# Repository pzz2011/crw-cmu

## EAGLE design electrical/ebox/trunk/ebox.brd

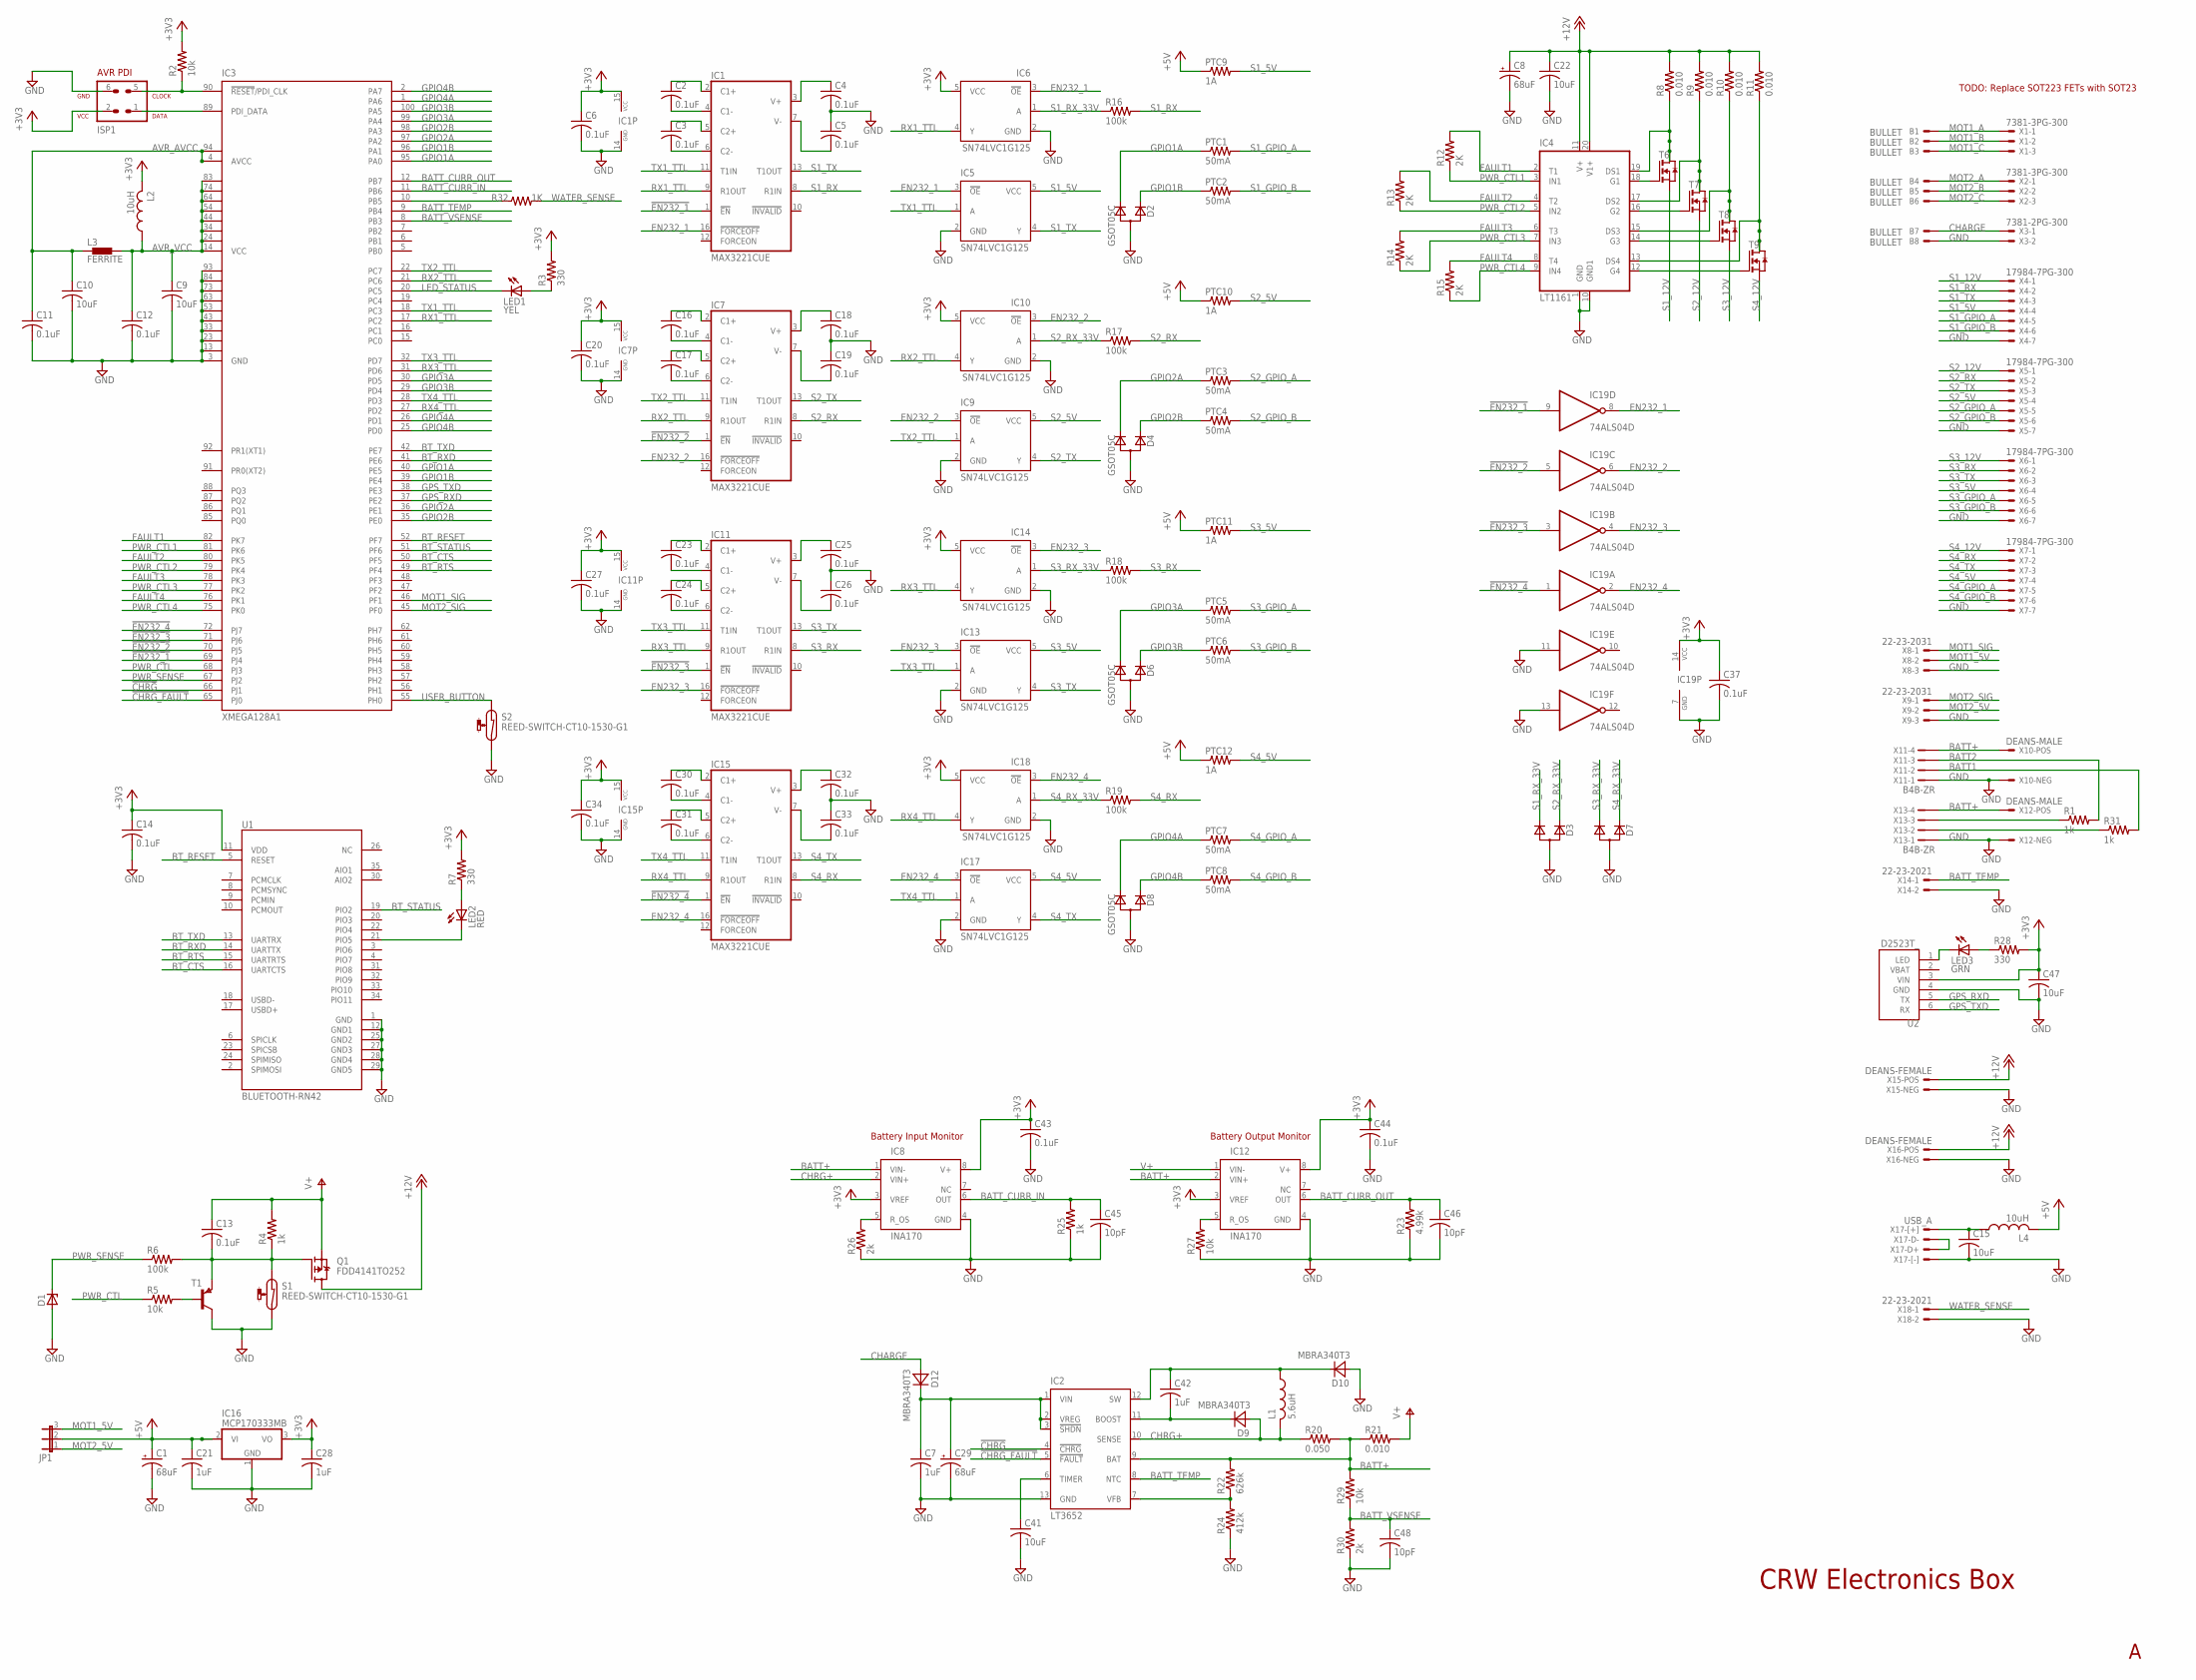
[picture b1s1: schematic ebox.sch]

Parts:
B1, B2, B3, B4, B5, B6, B7, B8: BULLET
C1, C8, C29: 68uF; PANASONIC_D
C2, C3, C4, C5, C6, C11, C12, C13, C14, C16, C17, C18, C19, C20, C23, C24, C25, C26, C27, C30, C31, C32, C33, C34, C37, C43, C44: 0.1uF; C0805
C7, C21, C28, C42: 1uF; C0805
C9, C10, C15, C22, C41, C47: 10uF; C0805
C45, C46, C48: 10pF; C0805
D1: ZENER-DIODESOT23; SOT23
D2, D4, D6, D8: GSOT05C; SOT-23
D3, D7: D_2CSOT23; SOT-23
D9, D10, D12: MBRA340T3; SMA
IC1, IC7, IC11, IC15: MAX3221CUE; TSSOP16
IC2: LT3652; MSOP12-MSE
IC3: XMEGA128A1; TQFP100
IC4: LT1161; SOIC20R
IC5, IC6, IC9, IC10, IC13, IC14, IC17, IC18: SN74LVC1G125; SOT23-DBV
IC8, IC12: INA170; MSOP8
IC16: MCP170333MB; SOT89
IC19: 74ALS04D; SO14
ISP1: AVR-PDIVERT; AVR-ISP-6
JP1: JP2E; JP2
L1: 5.6uH; IHLP-2020CZ-11
L2, L4: 10uH; L2012C
L3: FERRITE; 0402
LED1: YEL; CHIPLED_1206
LED2: RED; CHIPLED_1206
LED3: GRN; CHIPLED_1206
PTC1, PTC2, PTC3, PTC4, PTC5, PTC6, PTC7, PTC8: 50mA; R1206
PTC9, PTC10, PTC11, PTC12: 1A; R1206
Q1: FDD4141TO252; TO252
R1, R4, R25, R31: 1k; R0805
R2, R5, R27, R29: 10k; R0805
R3, R7, R28: 330; R0805
R6, R16, R17, R18, R19: 100k; R0805
R8, R9, R10, R11, R21: 0.010; R6332
R12, R13, R14, R15: 2K; R0805
R20: 0.050; R6332
R22: 626k; R0805
R23: 4.99k; R0805
R24: 412k; R0805
R26, R30: 2k; R0805
R32: 1K; R0805
S1, S2: REED-SWITCH-CT10-1530-G1; CT10-G1
T1: PNPSOT23; SOT-23
T6, T7, T8, T9: NMOSSOT23-6; SOT23-6
U1: BLUETOOTH-RN42; RN41
U2: D2523T_; EM406
X1, X2: 7381-3PG-300
X3: 7381-2PG-300
X4, X5, X6, X7: 17984-7PG-300
X8, X9: 22-23-2031
X10, X12: DEANS-MALE; DEANS_MALE
X11, X13: B4B-ZR
X14: 22-23-2021
X15, X16: DEANS-FEMALE; DEANS_FEMALE
X17: USB_A; 1001-002-01100
X18: 22-23-2021; MPN 22-23-2021

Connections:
3ROU: IC4.18 (G1), T6.4 (G)
!CHRG: IC2.4 (!CHRG), IC3.66 (PJ1)
!CHRG_FAULT: IC2.5 (!FAULT), IC3.65 (PJ0)
!EN232_1: IC1.1 (!EN), IC3.69 (PJ4), IC19.9 (I)
!EN232_2: IC3.70 (PJ5), IC7.1 (!EN), IC19.5 (I)
!EN232_3: IC3.71 (PJ6), IC11.1 (!EN), IC19.3 (I)
!EN232_4: IC3.72 (PJ7), IC15.1 (!EN), IC19.1 (I)
+3V3: C6.1, C14.1, C20.1, C27.1, C28.1, C34.1, C37.1, C43.1, C44.1, C47.1, IC1.15 (VCC), IC6.5 (VCC), IC7.15 (VCC), IC8.3 (VREF), IC8.8 (V+), IC10.5 (VCC), IC11.15 (VCC), IC12.3 (VREF), IC12.8 (V+), IC14.5 (VCC), IC15.15 (VCC), IC16.3 (VO), IC18.5 (VCC), IC19.14 (VCC), ISP1.2, L2.2, R2.2, R3.2, R7.2, R28.2, U1.11 (VDD), U2.3 (VIN)
+5V: C1.+, C21.1, IC16.2 (VI), IC16.2@1 (VI1), JP1.2, L4.2, PTC9.1, PTC10.1, PTC11.1, PTC12.1
+12V: C8.+, C22.1, IC4.11 (V+), IC4.20 (V1+), Q1.3 (D), R8.2, R9.2, R10.2, R11.2, X15.POS, X16.POS
AVR_AVCC: C10.1, C11.1, IC3.4 (AVCC), IC3.94 (AVCC1), L3.1
AVR_VCC: C9.1, C12.1, IC3.14 (VCC), IC3.24 (VCC1), IC3.34 (VCC2), IC3.44 (VCC3), IC3.54 (VCC4), IC3.64 (VCC5), IC3.74 (VCC6), IC3.83 (VCC7), L2.1, L3.2
BATT1: R31.2, X11.2
BATT2: R1.2, X11.3
BATT+: IC2.9 (BAT), IC8.1 (VIN-), IC12.2 (VIN+), R20.2, R21.1, R22.2, R29.2, X10.POS, X11.4, X12.POS, X13.4
BATT_CURR_IN: C45.1, IC3.11 (PB6), IC8.6 (OUT), R25.2
BATT_CURR_OUT: C46.1, IC3.12 (PB7), IC12.6 (OUT), R23.2
BATT_TEMP: IC2.8 (NTC), IC3.9 (PB4), X14.1
BATT_VSENSE: C48.1, IC3.8 (PB3), R29.1, R30.2
BT_CTS: IC3.50 (PF5), U1.16 (UARTCTS)
BT_RESET: IC3.52 (PF7), U1.5 (RESET)
BT_RTS: IC3.49 (PF4), U1.15 (UARTRTS)
BT_RXD: IC3.41 (PE6), U1.14 (UARTTX)
BT_STATUS: IC3.51 (PF6), U1.19 (PIO2)
BT_TXD: IC3.42 (PE7), U1.13 (UARTRX)
CHARGE: B7.P$1, D12.A, X3.1
CHRG+: D9.A, IC2.10 (SENSE), IC8.2 (VIN+), L1.2, R20.1
EN232_1: IC1.16 (!FORCEOFF), IC5.3 (!OE), IC6.3 (!OE), IC19.8 (O)
EN232_2: IC7.16 (!FORCEOFF), IC9.3 (!OE), IC10.3 (!OE), IC19.6 (O)
EN232_3: IC11.16 (!FORCEOFF), IC13.3 (!OE), IC14.3 (!OE), IC19.4 (O)
EN232_4: IC15.16 (!FORCEOFF), IC17.3 (!OE), IC18.3 (!OE), IC19.2 (O)
FAULT1: IC3.82 (PK7), IC4.2 (T1), R12.2
FAULT2: IC3.80 (PK5), IC4.4 (T2), R13.2
FAULT3: IC3.78 (PK3), IC4.6 (T3), R14.2
FAULT4: IC3.76 (PK1), IC4.8 (T4), R15.2
GND: B8.P$1, C1.-, C4.2, C5.1, C6.2, C7.2, C8.-, C9.2, C10.2, C11.2, C12.2, C14.2, C15.2, C18.2, C19.1, C20.2, C21.2, C22.2, C25.2, C26.1, C27.2, C28.2, C29.-, C32.2, C33.1, C34.2, C37.2, C41.2, C43.2, C44.2, C45.2, C46.2, C47.2, C48.2, D1.1 (A), D2.1 (A), D3.1 (A), D4.1 (A), D6.1 (A), D7.1 (A), D8.1 (A), D10.A, IC1.14 (GND), IC2.13 (GND), IC3.3 (GND), IC3.13 (GND1), IC3.23 (GND2), IC3.33 (GND3), IC3.43 (GND4), IC3.53 (GND5), IC3.63 (GND6), IC3.73 (GND7), IC3.84 (GND8), IC3.93 (GND9), IC4.1 (GND), IC4.10 (GND1), IC5.2 (GND), IC6.2 (GND), IC7.14 (GND), IC8.4 (GND), IC9.2 (GND), IC10.2 (GND), IC11.14 (GND), IC12.4 (GND), IC13.2 (GND), IC14.2 (GND), IC15.14 (GND), IC16.1 (GND), IC17.2 (GND), IC18.2 (GND), IC19.7 (GND), IC19.11 (I), IC19.13 (I), ISP1.6, R23.1, R24.1, R25.1, R26.1, R27.1, R30.1, S1.2, S2.2, T1.1 (C), U1.1 (GND), U1.12 (GND1), U1.25 (GND2), U1.27 (GND3), U1.28 (GND4), U1.29 (GND5), U2.4 (GND), X3.2, X4.7, X5.7, X6.7, X7.7, X8.3, X9.3, X10.NEG, X11.1, X12.NEG, X13.1, X14.2, X15.NEG, X16.NEG, X17.4, X18.2
GPIO1A: D2.3 (C2), IC3.40 (PE5), IC3.95 (PA0), PTC1.1
GPIO1B: D2.2 (C1), IC3.39 (PE4), IC3.96 (PA1), PTC2.1
GPIO2A: D4.3 (C2), IC3.36 (PE1), IC3.97 (PA2), PTC3.1
GPIO2B: D4.2 (C1), IC3.35 (PE0), IC3.98 (PA3), PTC4.1
GPIO3A: D6.3 (C2), IC3.30 (PD5), IC3.99 (PA4), PTC5.1
GPIO3B: D6.2 (C1), IC3.29 (PD4), IC3.100 (PA5), PTC6.1
GPIO4A: D8.3 (C2), IC3.1 (PA6), IC3.26 (PD1), PTC7.1
GPIO4B: D8.2 (C1), IC3.2 (PA7), IC3.25 (PD0), PTC8.1
GPS_RXD: IC3.37 (PE2), U2.5 (TX)
GPS_TXD: IC3.38 (PE3), U2.6 (RX)
LED_STATUS: IC3.20 (PC5), LED1.C
LED_STATUS1: LED2.C, U1.21 (PIO5)
MOT1_5V: JP1.3, X8.2
MOT1_A: B1.P$1, X1.1
MOT1_B: B2.P$1, X1.2
MOT1_C: B3.P$1, X1.3
MOT1_SIG: IC3.46 (PF1), X8.1
MOT2_5V: JP1.1, X9.2
MOT2_A: B4.P$1, X2.1
MOT2_B: B5.P$1, X2.2
MOT2_C: B6.P$1, X2.3
MOT2_SIG: IC3.45 (PF0), X9.1
unnamed: C2.2, IC1.4 (C1-)
unnamed: C2.1, IC1.2 (C1+)
unnamed: C3.1, IC1.5 (C2+)
unnamed: C3.2, IC1.6 (C2-)
unnamed: IC3.90 (!RESET!/PDI_CLK), ISP1.5, R2.1
unnamed: LED1.A, R3.1
unnamed: IC3.89 (PDI_DATA), ISP1.1
unnamed: R5.2, T1.3 (B)
unnamed: LED2.A, R7.1
unnamed: C4.1, IC1.3 (V+)
unnamed: C5.2, IC1.7 (V-)
unnamed: IC4.19 (DS1), R8.1, T6.1 (D), T6.2 (D1), T6.5 (D2), T6.6 (D3)
unnamed: C13.2, Q1.1 (G), R4.1, R6.2, S1.1, T1.2 (E)
unnamed: IC4.17 (DS2), R9.1, T7.1 (D), T7.2 (D1), T7.5 (D2), T7.6 (D3)
unnamed: IC4.15 (DS3), R10.1, T8.1 (D), T8.2 (D1), T8.5 (D2), T8.6 (D3)
unnamed: IC4.13 (DS4), R11.1, T9.1 (D), T9.2 (D1), T9.5 (D2), T9.6 (D3)
unnamed: IC3.10 (PB5), R32.1
unnamed: IC4.16 (G2), T7.4 (G)
unnamed: IC4.14 (G3), T8.4 (G)
unnamed: IC4.12 (G4), T9.4 (G)
unnamed: C16.2, IC7.4 (C1-)
unnamed: C16.1, IC7.2 (C1+)
unnamed: C17.2, IC7.6 (C2-)
unnamed: C17.1, IC7.5 (C2+)
unnamed: C18.1, IC7.3 (V+)
unnamed: C19.2, IC7.7 (V-)
unnamed: C23.2, IC11.4 (C1-)
unnamed: C23.1, IC11.2 (C1+)
unnamed: C24.2, IC11.6 (C2-)
unnamed: C24.1, IC11.5 (C2+)
unnamed: C25.1, IC11.3 (V+)
unnamed: C26.2, IC11.7 (V-)
unnamed: C30.2, IC15.4 (C1-)
unnamed: C30.1, IC15.2 (C1+)
unnamed: C31.2, IC15.6 (C2-)
unnamed: C31.1, IC15.5 (C2+)
unnamed: C32.1, IC15.3 (V+)
unnamed: C33.2, IC15.7 (V-)
unnamed: C41.1, IC2.6 (TIMER)
unnamed: C15.1, L4.1, X17.1
unnamed: C42.2, D9.C, IC2.11 (BOOST)
unnamed: C42.1, D10.C, IC2.12 (SW), L1.1
unnamed: LED3.C, U2.1 (LED)
unnamed: IC2.7 (VFB), R22.1, R24.2
unnamed: X17.2, X17.3
unnamed: R1.1, X13.3
unnamed: C7.1, C29.+, D12.C, IC2.1 (VIN), IC2.2 (VREG), IC2.3 (!SHDN)
unnamed: IC8.5 (R_OS), R26.2
unnamed: IC12.5 (R_OS), R27.2
unnamed: LED3.A, R28.1
unnamed: R31.1, X13.2
PWR_CTL: IC3.68 (PJ3), R5.1
PWR_CTL1: IC3.81 (PK6), IC4.3 (IN1), R12.1
PWR_CTL2: IC3.79 (PK4), IC4.5 (IN2), R13.1
PWR_CTL3: IC3.77 (PK2), IC4.7 (IN3), R14.1
PWR_CTL4: IC3.75 (PK0), IC4.9 (IN4), R15.1
PWR_SENSE: D1.3 (C), IC3.67 (PJ2), R6.1
RX1_TTL: IC1.9 (R1OUT), IC3.17 (PC2), IC6.4 (Y)
RX2_TTL: IC3.21 (PC6), IC7.9 (R1OUT), IC10.4 (Y)
RX3_TTL: IC3.31 (PD6), IC11.9 (R1OUT), IC14.4 (Y)
RX4_TTL: IC3.27 (PD2), IC15.9 (R1OUT), IC18.4 (Y)
S1_5V: IC5.5 (VCC), PTC9.2, X4.4
S1_12V: T6.3 (S), X4.1
S1_GPIO_A: PTC1.2, X4.5
S1_GPIO_B: PTC2.2, X4.6
S1_RX: IC1.8 (R1IN), R16.2, X4.2
S1_RX_33V: D3.3 (C2), IC6.1 (A), R16.1
S1_TX: IC1.13 (T1OUT), IC5.4 (Y), X4.3
S2_5V: IC9.5 (VCC), PTC10.2, X5.4
S2_12V: T7.3 (S), X5.1
S2_GPIO_A: PTC3.2, X5.5
S2_GPIO_B: PTC4.2, X5.6
S2_RX: IC7.8 (R1IN), R17.2, X5.2
S2_RX_33V: D3.2 (C1), IC10.1 (A), R17.1
S2_TX: IC7.13 (T1OUT), IC9.4 (Y), X5.3
S3_5V: IC13.5 (VCC), PTC11.2, X6.4
S3_12V: T8.3 (S), X6.1
S3_GPIO_A: PTC5.2, X6.5
S3_GPIO_B: PTC6.2, X6.6
S3_RX: IC11.8 (R1IN), R18.2, X6.2
S3_RX_33V: D7.3 (C2), IC14.1 (A), R18.1
S3_TX: IC11.13 (T1OUT), IC13.4 (Y), X6.3
S4_5V: IC17.5 (VCC), PTC12.2, X7.4
S4_12V: T9.3 (S), X7.1
S4_GPIO_A: PTC7.2, X7.5
S4_GPIO_B: PTC8.2, X7.6
S4_RX: IC15.8 (R1IN), R19.2, X7.2
S4_RX_33V: D7.2 (C1), IC18.1 (A), R19.1
S4_TX: IC15.13 (T1OUT), IC17.4 (Y), X7.3
TX1_TTL: IC1.11 (T1IN), IC3.18 (PC3), IC5.1 (A)
TX2_TTL: IC3.22 (PC7), IC7.11 (T1IN), IC9.1 (A)
TX3_TTL: IC3.32 (PD7), IC11.11 (T1IN), IC13.1 (A)
TX4_TTL: IC3.28 (PD3), IC15.11 (T1IN), IC17.1 (A)
USER_BUTTON: IC3.55 (PH0), S2.1
V+: C13.1, IC12.1 (VIN-), Q1.2 (S), R4.2, R21.2
WATER_SENSE: R32.2, X18.1

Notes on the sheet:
CRW Electronics Box
Battery Input Monitor
Battery Output Monitor
TODO: Replace SOT223 FETs with SOT23

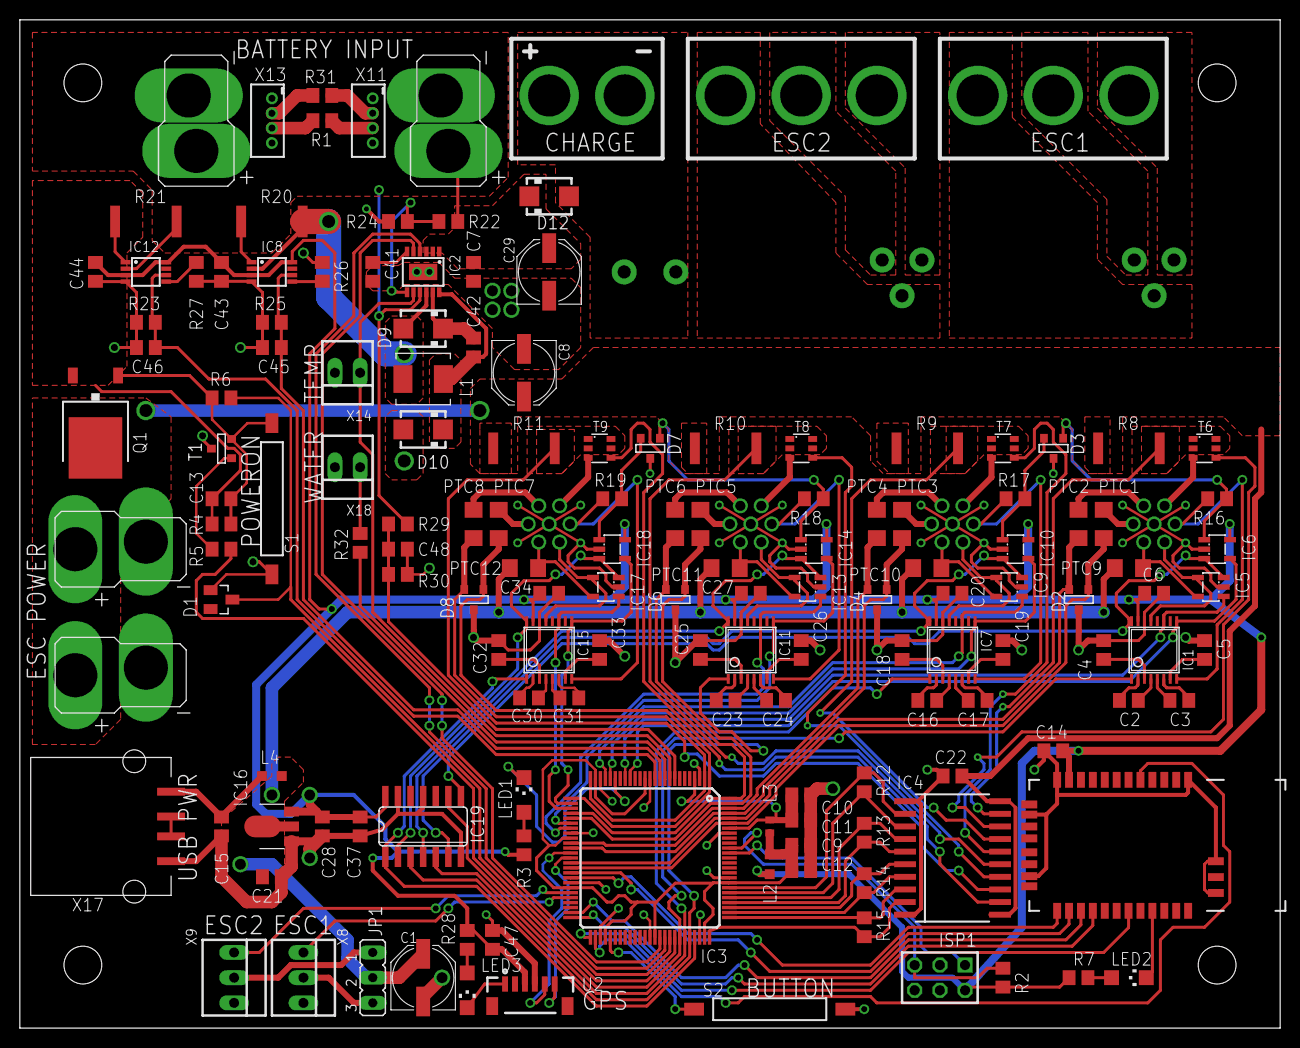
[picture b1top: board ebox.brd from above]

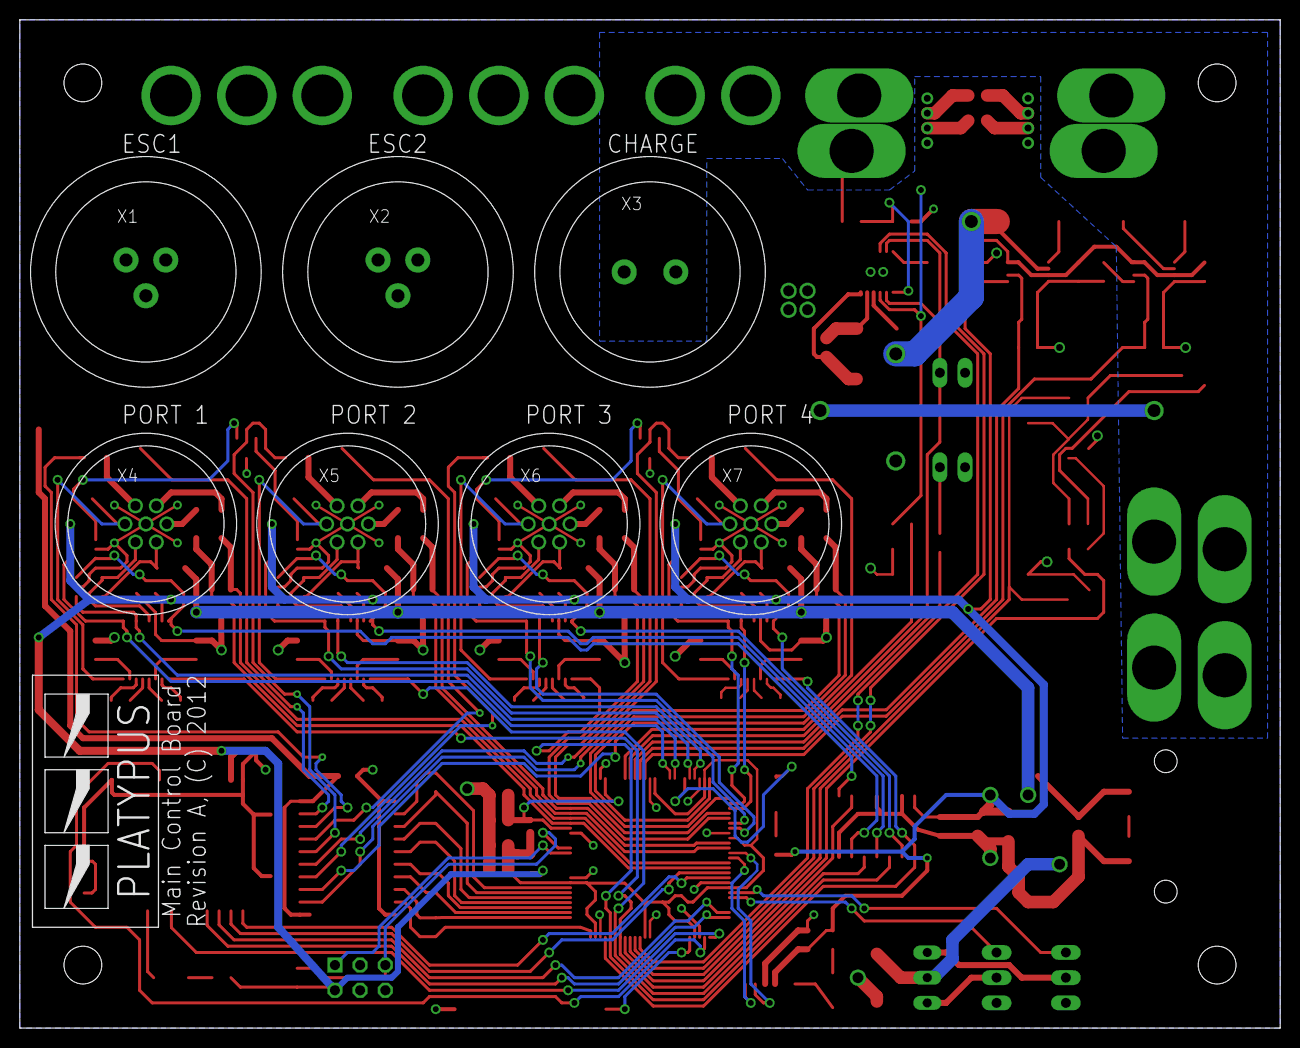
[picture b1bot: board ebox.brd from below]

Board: 2 copper layers, 127.0 x 101.6 mm, 162 parts (8 on the bottom side), 154 nets.

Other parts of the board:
U$1: PLATYPUS_LOGO; PLATYPUS_LOGO_SMALL

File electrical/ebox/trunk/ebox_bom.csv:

"Qty";"Value";"Device";"Package";"Parts";"Description";"MF";"MPN";"OC_FARNELL";"OC_NEWARK";
"2";"";"D_2CSOT23";"SOT-23";"D3, D7";"Dual DIODE";"";"";"unknown";"unknown";
"1";"";"JP2E";"JP2";"JP1";"JUMPER";"";"";"";"";
"4";"";"NMOSSOT23-6";"SOT23-6";"T6, T7, T8, T9";"MOS FET";"";"";"unknown";"unknown";
"1";"";"PNPSOT23";"SOT-23";"T1";"PNP TRANSISTOR";"";"DSS20200L-7";"unknown";"25R4554";
"1";"";"ZENER-DIODESOT23";"SOT23";"D1";"Z-Diode";"";"";"";"";
"5";"0.010";"R-US_R6332";"R6332";"R8, R9, R10, R11, R21";"RESISTOR, American symbol";"";"";"";"";
"1";"0.050";"R-US_R6332";"R6332";"R20";"RESISTOR, American symbol";"";"";"";"";
"27";"0.1uF";"C-USC0805";"C0805";"C2, C3, C4, C5, C6, C11, C12, C13, C14, C16, C17, C18, C19, C20, C23, C24, C25, C26, C27, C30, C31, C32, C33, C34, C37, C43, C44";"CAPACITOR, American symbol";"";"";"";"";
"5";"100k";"R-US_R0805";"R0805";"R6, R16, R17, R18, R19";"RESISTOR, American symbol";"";"";"";"";
"4";"10k";"R-US_R0805";"R0805";"R2, R5, R27, R29";"RESISTOR, American symbol";"";"";"";"";
"3";"10pF";"C-USC0805";"C0805";"C45, C46, C48";"CAPACITOR, American symbol";"";"";"";"";
"6";"10uF";"C-USC0805";"C0805";"C9, C10, C15, C22, C41, C47";"CAPACITOR, American symbol";"";"";"";"";
"2";"10uH";"L-USL2012C";"L2012C";"L2, L4";"INDUCTOR, American symbol";"";"";"";"";
"4";"17984-7PG-300";"17984-7PG-300";"17984-7PG-300";"X4, X5, X6, X7";"MICRO-CON-X® FIELD INSTALLABLE CONNECTOR";"";"";"";"";
"4";"1A";"R-US_R1206";"R1206";"PTC9, PTC10, PTC11, PTC12";"RESISTOR, American symbol";"";"";"";"";
"1";"1K";"R-US_R0805";"R0805";"R32";"RESISTOR, American symbol";"";"";"";"";
"4";"1k";"R-US_R0805";"R0805";"R1, R4, R25, R31";"RESISTOR, American symbol";"";"";"";"";
"4";"1uF";"C-USC0805";"C0805";"C7, C21, C28, C42";"CAPACITOR, American symbol";"";"";"";"";
"2";"22-23-2021";"22-23-2021";"22-23-2021";"X14, X18";".100" (2.54mm) Center Header - 2 Pin";"MOLEX";"22-23-2021";"1462926";"25C3832";
"2";"22-23-2031";"22-23-2031";"22-23-2031";"X8, X9";".100" (2.54mm) Center Header - 3 Pin";"MOLEX";"22-23-2031";"1462950";"30C0862";
"4";"2K";"R-US_R0805";"R0805";"R12, R13, R14, R15";"RESISTOR, American symbol";"";"";"";"";
"2";"2k";"R-US_R0805";"R0805";"R26, R30";"RESISTOR, American symbol";"";"";"";"";
"3";"330";"R-US_R0805";"R0805";"R3, R7, R28";"RESISTOR, American symbol";"";"";"";"";
"1";"4.99k";"R-US_R0805";"R0805";"R23";"RESISTOR, American symbol";"";"";"";"";
"1";"412k";"R-US_R0805";"R0805";"R24";"RESISTOR, American symbol";"";"";"";"";
"1";"5.6uH";"IHLP-2020CZ-11";"IHLP-2020CZ-11";"L1";"";"";"";"";"";
"8";"50mA";"R-US_R1206";"R1206";"PTC1, PTC2, PTC3, PTC4, PTC5, PTC6, PTC7, PTC8";"RESISTOR, American symbol";"";"";"";"";
"1";"626k";"R-US_R0805";"R0805";"R22";"RESISTOR, American symbol";"";"";"";"";
"3";"68uF";"CPOL-USD";"PANASONIC_D";"C1, C8, C29";"POLARIZED CAPACITOR, American symbol";"";"";"";"";
"1";"7381-2PG-300";"7381-2PG-300";"7381-2PG-300";"X3";"";"";"";"";"";
"2";"7381-3PG-300";"7381-3PG-300";"7381-3PG-300";"X1, X2";"Mini-Con-X Panel Connector";"";"";"";"";
"1";"74ALS04D";"74ALS04D";"SO14";"IC19";"Hex INVERTER";"";"";"";"";
"1";"AVR-PDIVERT";"AVR-PDIVERT";"AVR-ISP-6";"ISP1";"AVR PDI programming interface connector";"";"";"";"";
"2";"B4B-ZR";"B4B-ZR";"B4B-ZR";"X11, X13";"ZH CONNECTOR 1.5 mm, 4 pin 1 row";"FARNELL";"B4B-ZR(LF)(SN)";"1830916";"37K9960";
"1";"BLUETOOTH-RN42";"BLUETOOTH-RN41"";"RN41";"U1";"Bluetooth SMD module";"";"";"";"";
"8";"BULLET";"BULLET";"BULLET";"B1, B2, B3, B4, B5, B6, B7, B8";"Bullet Connector";"";"";"";"";
"1";"D2523T_";"D2523T_";"EM406";"U2";"D2523T GPS Module";"";"";"";"";
"2";"DEANS-FEMALE";"DEANS-FEMALE";"DEANS_FEMALE";"X15, X16";"Deans Battery Connector";"";"";"";"";
"2";"DEANS-MALE";"DEANS-MALE";"DEANS_MALE";"X10, X12";"Deans Battery Connector";"";"";"";"";
"1";"FDD4141TO252";"FDD4141TO252";"TO252";"Q1";"P-Channel PowerTrench® MOSFET";"";"";"";"";
"1";"FERRITE";"BML15HB121SN1";"0402";"L3";"EMIFIL (R) Chip Ferrite Bead for GHz Noise";"";"";"";"";
"1";"GRN";"LEDCHIPLED_1206";"CHIPLED_1206";"LED3";"LED";"";"";"";"";
"4";"GSOT05C";"D_2CSOT23";"SOT-23";"D2, D4, D6, D8";"Dual DIODE";"";"";"unknown";"unknown";
"2";"INA170";"INA170";"MSOP8";"IC8, IC12";"High-Side, Bidirectional";"";"";"";"";
"1";"LT1161";"LT1161";"SOIC20R";"IC4";"Single-Supply 16-Bit Stereo ADC";"";"";"";"";
"1";"LT3652";"LT3652";"MSOP12-MSE";"IC2";"2-Channel, 12-Bit ADC with I2C-Compatible Interface 10-Lead MSOP";"";"AD7992BRMZ-0";"1078311";"31M4422";
"4";"MAX3221CUE";"MAX3221CUE";"TSSOP16";"IC1, IC7, IC11, IC15";"RS-232 Transceivers with AutoShutdown";"MAXIM";"MAX3221CUE+";"1379915";"68K4608";
"3";"MBRA340T3";"MBRA340T3";"SMA";"D9, D10, D12";"Surface Mount Schottky Power Rectifier";"";"";"";"";
"1";"MCP170333MB";"MCP170333MB";"SOT89";"IC16";"250 mA, 16V, Low Quiescent Current LDO Regulator";"";"";"";"";
"1";"PLATYPUS_LOGO";"PLATYPUS_LOGO";"PLATYPUS_LOGO_SMALL";"U$1";"";"";"";"";"";
"1";"RED";"LEDCHIPLED_1206";"CHIPLED_1206";"LED2";"LED";"";"";"";"";
"2";"REED-SWITCH-CT10-1530-G1";"REED-SWITCH-CT10-1530-G1";"CT10-G1";"S1, S2";"Reed Sensor";"COTO TECHNOLOGY";"CT10-1530-G1";"1081696";"";
"8";"SN74LVC1G125";"SN74LVC1G125";"SOT23-DBV";"IC5, IC6, IC9, IC10, IC13, IC14, IC17, IC18";"SINGLE BUS BUFFER GATE WITH 3-STATE OUTPUT";"";"";"";"";
"1";"USB_A";"USB_A";"1001-002-01100";"X17";"USB A-type connector";"";"";"";"";
"1";"XMEGA128A1";"XMEGA128A1";"TQFP100";"IC3";"MICROCONTROLLER";"";"";"unknown";"unknown";
"1";"YEL";"LEDCHIPLED_1206";"CHIPLED_1206";"LED1";"LED";"";"";"";"";

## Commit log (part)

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2012-11-01 Added board and some of layout.
2012-11-02 Added svn:ignore for temp files.
2012-11-02 I thought we just committed the changes to the footprints, but apparently we didn't.
2012-11-02 Adding tags and trunk structure to ebox.
2012-11-02 Moved ebox parts to trunk folder.
2012-11-02 We don't use avr7 microcontrollers.
2012-11-02 Made a tag of the point where system is feature complete, will be simplifying from here out.
2012-11-02 Removed switching regulators, replaced with onboard ESC BEC power.
2012-11-02 Added missing battery connectors for ESC.
2012-11-04 Added USB connector, swapped FETs for smaller form factor.
2012-11-07 Most of power layout is done too.
2012-11-13 Placed all components on board.
2012-11-16 Added rest of routing for much of power section.
2012-11-16 Loads better routing of power.
2012-11-16 Fixed sensor routing, couple of other things.
2012-11-16 More routing finished, under 100 airwires.
2012-11-18 All high power routing is sufficient. Tuning routing on digital lines.
2012-11-18 Almost all digital routing completed and checked. Need to do pwr ctrl and enable lines.
2012-11-18 All signal wiring to MCU stable. Just need to do enable lines and clean up.
2012-11-19 Added water sensor connection.
2012-11-19 Fixed last few airwires, on to trace optimization for a bit.
2012-11-19 Cleaned up more stuff. Just need to do final check and silkscreen work.
2012-11-19 Updated some silkscreen on various areas.
2012-11-19 Silkscreening complete. Prepped for DFM check.
2012-11-19 Fixed thermal reliefs in board.
2012-11-19 Gerber/excellon files for board.
2012-11-19 Oops, wrong component file.
2012-11-19 Fixed copper pour insufficient spacing issues.
2012-11-19 Updated for more DFM corrections.
2012-11-20 Added bill of materials.
2012-11-20 Added excel file with full parts list.
2012-11-20 Added as-built for revision A of ebox board.
2012-12-12 Added tag for last Arduino-based firmware, new firmware will be for custom PCBs.
2012-12-12 Added new source directory for firmware to handle all the new stuff. Changed build system to AVR.
2012-12-12 Moved all the source files to source directory.
2012-12-12 Moved cpp files to new source directory for firmware.
2012-12-12 Added main function as entry point.
2012-12-12 Renamed a whole bunch of source files to match new firmware organization.
2012-12-12 Added placeholder for board definition files.
2012-12-12 Adapted the Makefile to begin to do what we want.
2012-12-17 Changed old main file so syntax highlighting works.
2012-12-17 Removed windows-style line endings from serial header.
2012-12-17 Organized files into hardware and system folders to cleanup main source tree.
2012-12-17 Added header files for all the system components (previously automagically handled by Arduino?)
2012-12-17 Made modifications to add Netbeans project for the firmware. It is NOT required to compile the firmware.
2012-12-17 Cleaned up project configuration.
2012-12-21 Cleaned up project configuration more, added working LED driver, restructured netbeans project to actually show useful stuff.
2012-12-21 Added port of eeprom reads and writes, i think.
2012-12-21 Added better eeprom port.
2012-12-21 Ok, starting to get reasonably compilable. Still need to figure out how the heck to templatize serial stuff.
2012-12-25 Major overhaul to serial code structure that will hopefully resolve most of this mess with the multiple serial ports being used.
2012-12-25 Major overhaul to IO system. Trying to get things under control again w.r.t. firmware structure.
2012-12-25 Minor patch to get I2c driver in line.
2012-12-30 Added new cleaned up servo handling code, similar to serial fix. Just need to do the same for a timer callback and we should be in business.
2012-12-30 Added general purpose task timer (for regular execution of control loops). I think at this point we mostly just need to pipe it all up and cross our fingers.
2012-12-30 Added CPU frequency macro.
2012-12-30 Fixed board macro.
2012-12-30 Configured system to use 32Mhz clock and adjusted servo timings.
2012-12-30 Theoretically, configured all the serial baud rate stuff. We'll see if this works or not...
2012-12-31 Successful LED test at 32Mhz clock rate.
2012-12-31 I think this should fix all the correct port values now and fix the memory references necessary for the hardware template modules.
2012-12-31 Tested and confirmed task timer and led port config as working properly.
2012-12-31 Restored Arduino-like function structure to firmware. First step of combining all the ported code together.
2012-12-31 Added motor servo to board configuration file.
2012-12-31 Serial port is operating normally, committed my port of amarino... we'll see how THAT goes...
2012-12-31 Added amarino to compile list. Fixed bug where it was sending a slash and an N instead of a newline. HOW DID THIS CODE EVER WORK BEFORE??
2012-12-31 Fixed some bugs in the servo code. That part should be operational now.
2012-12-31 Fixed errors in eeprom read/write.
2012-12-31 Completed port of rudder control code.
2012-12-31 Configured the thruster and patched a couple of things in the rudder system.
2013-01-01 Changed all the naming conventions to c++ for sensors.
2013-01-01 Restructured sensors to use the template system. It's not ideal, but it will have to do for now.
2013-01-02 Changed main function to have the sensor includes and some more comments.
2013-01-02 Did a major rework of entire servo system in order to make all sensor ports work (needed for rudder to work properly).
2013-01-02 Overhauled all system functions to clean up implementations of stuff. This should make sensors more reasonable to handle.. I hope...
2013-01-02 Moved portability with the other system stuff.
2013-01-02 Added more baud rates for all the sensors.
2013-01-02 Cleaned up a fair bit with depth sensor. Need to figure out how to replace std:string.
2013-01-02 Got DO sensor compiling as well. That's two out of three.. Unfortunately 5TE is the horrible messy one.
2013-01-02 Removed pseudothread stuff and got 5TE compiling. Seems reasonable...
2013-01-02 Ok, everything should be mostly ready for testing tomorrow, I think.
2013-01-02 Added pin configurations to properly power the depth sensor.
2013-01-02 End user
2013-01-02 Added abstract sensor interface and cleaned up main code a bit more.
2013-01-02 Cleaned up SAFE code that should start things up and be nice and clean.
2013-01-02 Added minor fix to LED hardware driver.
2013-01-02 Added correct thruster arming sequence.
2013-01-02 Added fuse programming to makefile to fix EEPROM not saving bug.
2013-01-02 Fixed minor bug in serial.
2013-01-02 Added CTS line fix to board initialization (for bluetooth).
2013-01-04 Almost complete "enduser"
2013-01-06 Entropy planner
2013-01-07 Added "advanced" data display popup.
2013-01-09 Clean up
2013-01-14 Added several additional map layers, including high-res Virtual Earth layer to MRC World Wind widget
2013-01-14 Cleaned up serial code a bit, but functionality shouldn't change at all.
2013-01-15 Reset PID constants to unscaled values (just realized that we deprecated this functionality because it is all done on the phone now.)
2013-01-15 Moved trunk (pre-controller code) out to make room for controller_dev branch to merge as new trunk.
2013-01-15 Moved controller dev to be the new trunk for server code.
2013-01-15 Compatibility mods to work with latest ADT bundle.
2013-01-15 Moved trunk back to branch, we don't want that.
2013-01-15 Moved old trunk back, we want this.
2013-01-15 Removed old trunk. It is just not compatible with new code.
2013-01-15 Created a new trunk from controller_dev.
2013-01-15 Cleaned up the code to use normalized control values for thrust and rudder.
2013-01-15 Changed gains and timings to their final version for actuators.
2013-01-16 Fixed drive panel to use relative -100-100% commands.
2013-01-16 Changed direction of shroud rotation to match +Z frame.
2013-01-16 Reversed inverted rudder mapping (no need for that!)
2013-01-17 Model button not enabled until area set.
2013-01-17 Changed button text in ConfigureBoats frame
2013-01-17 Added Virtual Earth layer
2013-01-19 Re-inverted rudder axis (apparently it was reversed after all?). This way PID values should remain positive.
2013-01-20 Fixed camera in Enduser
2013-01-20 Created virtual earth layer from copy
2013-01-22 Labels on Drive Panel
2013-01-22 Improved line drawing behavior
2013-01-30 Go slow
2013-02-11 Bug for small areas running grid
2013-02-18 Added synchronized to intelligence algorithm to prevent occasional lock
2013-02-18 Added safety condition to intelligence algorithm to prevent occasional lock
2013-02-20 Tested working 5TE sensor (minor fixes to pinout).
2013-02-20 Removed warning for 5TE pinout (fixed).
2013-02-20 Added ES2 sensor.
2013-02-21 ES-2 fixes
2013-02-26 Sensor parsing
2013-02-26 Sensors
2013-02-26 DO fix
2013-02-26 Fixed bug with C/Java string formatting in DO sensor Updated r_PID and CONST_THRUST values for Lutra model boat
2013-03-10 Minor fix to get rid of one-character buffer overflow causing depth sensor to fail checksum.
2013-03-12 Added new branch for next gen ebox board.
2013-03-12 Added new project for new board.
2013-03-12 Added new library for new ebox components.
2013-03-12 Added initial schematic with TODO list on it.
2013-03-21 Updated configurations to make this a valid netbeans 7.3 project.
2013-04-17 Added some docs for new connectors and started making footprints.
2013-04-21 Added new library footprints for conxall everything.
2013-04-21 Added big profet footprint and symbol.
2013-04-21 Added docs and footprints for profets.
2013-04-23 Added transceiver for RS232.
2013-04-23 Added docs for transceiver.
2013-04-23 Added power poles to platypus library.
2013-04-26 Added boilerplate for monitor instruments sensor.
2013-04-26 Added sensor string size change (hopefully we don't stack overflow!)
2013-04-26 Added implementation for monitor instruments unit.
2013-05-06 Removed controller branch (it's not doing anything for us).
2013-05-06 Renamed gates in platypus.lbr.
2013-05-23 Created new branch for monitor instruments development
2013-05-23 Added thruster2 stuff.
2013-05-23 Almost owrking but still some weird bugs.
2013-05-24 Stripped out useless EEPROM values.
2013-05-24 Oops, fixed bug where I was outputting on channel C instead of channel A!
2013-05-24 Added fix for mixing in rudder signal.
2013-05-24 Fixed minor parsing bug in monitor instrument.
2013-05-25 Cleaned up the main code for Monitor instruments firmware rev.
2013-05-25 Fixed bug where sensor messages terminated with newlines and there was an overflow in the size of messages.
2013-06-03 Added backport for monitor instruments serial fix.
2013-06-03 Fixed arming sequence missing bug and out-of-range motor cutout problem.
2013-06-03 Added solder paste settings to DRC in ebox revA EAGLE files.
2013-06-03 Took out debugging print statement and added fix to use thrust PIDs in controller.
2013-06-06 Added limits to thrust on mass spec boat
2013-06-06 Increased the number of sensors to 5
2013-06-11 Various minor, including fixes for hostname bug
2013-06-24 Fixed bug in loadVehicleLog.m, was including {'s in the parsed numbers
2013-08-22 Patched behavior of network resolution to work in newer JDK 1.7 VMs. (The injectHostname bug).
2013-08-22 Updated core library to be a new build with the hostname fix.
2013-08-22 Fixed incorrectly constructed path to CopyLibs dependency.
2013-08-22 Fixed build of crwclient to use newer core (should not change anything).
2013-09-01 Replaced 64-bit libraries with latest jogl 1.1.1a.
2013-09-01 Fixed bug where initial boatproxy server address was formatted incorrectly, and corresponding bug where null hostnames would cause null pointer exceptions.
2013-09-04 - Added sensor data widget to enduser operator console
2013-09-10 Added voltage/current sensing to boards.
2014-03-05 Reenabled gains in GUI (I think this is reasonable to do now?).
2014-03-05 Changed main to use debug panel instead of deprecated Debugger.
2014-03-09 Changed default class back to airboatdebugger (panel doesn't have an IP address for the boats).

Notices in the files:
electrical/ebox/trunk/ebox.brd:
Revision A, (C) 2012
parts and their libraries:
SparkFun-RF: Licensing: CC v3.0 Share-Alike You are welcome to use this library for commercial purposes.
